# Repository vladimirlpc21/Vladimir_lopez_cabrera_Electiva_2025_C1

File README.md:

# Repositorio-de-Git-para-Electiva_C1_2025

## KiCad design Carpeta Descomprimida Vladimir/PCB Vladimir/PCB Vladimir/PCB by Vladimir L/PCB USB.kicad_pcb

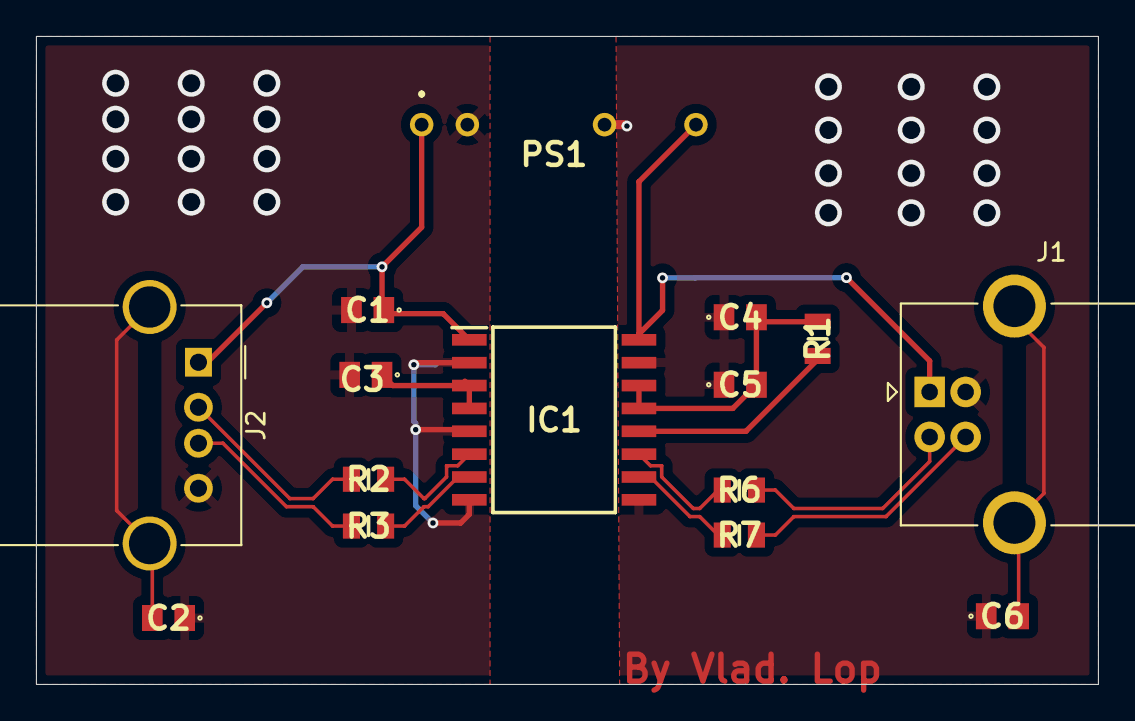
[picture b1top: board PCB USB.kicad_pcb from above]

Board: 2 copper layers, 59.0 x 36.0 mm, 15 parts (0 on the bottom side), 17 nets.

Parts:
C1, C2, C3, C4, C5, C6: 0.1uF; C0805
IC1: ADUM3160BRWZ-RL; SOIC127P1032X265-16N
J1: USB_B; USB_B_OST_USB-B1HSxx_Horizontal
J2: USB_A; USB_A_Molex_67643_Horizontal
PS1: TEA_1-0505HI; TEA10505HI
R1: 10kohm; RESC2012X55N
R2, R3, R6, R7: 24; RESC2012X60N

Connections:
DD+: J1.3 (D+), R7.2
DD-: J1.2 (D-), R6.2
D_D+: IC1.10 (DD+), R7.1
D_D-: IC1.11 (DD-), R6.1
GND: C1.2, C2.1, C3.2, IC1.2 (GND1_1), IC1.5 (SPU), IC1.8 (GND1_2), J2.4 (GND), PS1.2 (-VIN_(GND))
GNDS: C4.1, C5.1, C6.1, IC1.9 (GND2_1), IC1.15 (GND2_2), J1.4 (GND), PS1.5 (-VOUT)
unnamed: C3.1, IC1.3 (VDD1), IC1.4 (PDEN)
unnamed: IC1.12 (PIN), R1.2
unnamed: C4.2, C5.2, IC1.13 (SPD), IC1.14 (VDD2), R1.1
unnamed: C6.2, J1.5 (Shield)
unnamed: C2.2, J2.5 (Shield)
UD+: J2.3 (D+), R3.1
UD-: J2.2 (D-), R2.1
U_D+: IC1.7 (UD+), R3.2
U_D-: IC1.6 (UD-), R2.2
VBUS: C1.1, IC1.1 (VBUS), J2.1 (VBUS), PS1.1 (+VIN_(VCC))
VBUS2: IC1.16 (VBUS2), J1.1 (VBUS), PS1.7 (+VOUT)

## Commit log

2025-01-24 Add files via upload
    Diseño practica Kidcad del video
2025-01-24 Diseño kidcad
    Diseño kidcad Youtube
2025-03-27 PCB DE USB Vladimir lopez
2025-03-27 Resumenes Electiva
2025-04-07 Kicad usb
2025-04-07 Add files via upload
    Kicad USB
2025-04-25 Diseño Final Electiva 2025
    Diseño final de cuatrimestre
2025-04-26 Especificaciones del proyecto.
2025-04-26 Plano de medida de el equipo
2025-04-27 Pieza PLC soli edge Comunity Electiva
2025-04-29 Archives para Correction
2025-06-02 Resumen prueba 1
